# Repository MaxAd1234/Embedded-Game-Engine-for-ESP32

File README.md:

# Realization of an embedded game engine using real-time operating systems

This is a game engine for ESP32 boards demonstrating how real-time operating systems (RTOSs) and their concepts can be used for game development on microcontrollers. The game engine is part of my bachelor's thesis. It can be used as a base for developing games on microcontrollers like the ESP32.

## Demos

### Bird Game

### Pong clone

## Features
The game engine supports the following features:
- 2D-Tilemap-Rendering
- Four different input types (press, release, hold and hold for a specific time)
- Texture and audio storage
- 8-bit-style audio support for background music and sound effects
- Box and circle colliders
- Simple physics for gravity and forces
- Game programming interface
- Game objects as the base for game elements
- 2D Vectors
- Dynamic frame rate adaptation

## Tech Stack
- ESP-IDF
- C++
- FreeRTOS
- KiCad for the PCB

## Table of Contents

- [Demos](#demos)
- [Features](#features)
- [Getting Started](#getting-started)
  - [Hardware prerequisites](#hardware-prerequisites)
  - [Software prerequisites](#software-prerequisites)
  - [Example games](#example-games)
  - [How to set up](#how-to-set-up)
  - [Coordinate system](#coordinate-system)
- [How the Game Engine works](#how-the-game-engine-works)
  - [Architecture](#architecture)
  - [Input handling](#input-handling)
- [Components and features](#components-and-features)
  - [Input](#input)
  - [Graphics](#graphics)
  - [Audio](#audio)
  - [Collision](#collision)
  - [Physics](#physics)
  - [Level Design](#level-design)
  - [Game objects](#game-objects)
  - [Main Game Interface](#main-game-interface)
- [Further documentation and architecture](#further-documentation-and-architecture)
- [License](#license)

## Getting Started
### Hardware prerequisites
The game engine was built for a handheld using the following parts. Other parts could be used, but eventually the code needs to be adapted (e.g., the panels and the data bus configuration must be changed when using another display).

**Used parts**
- 6 push buttons
- DFRobot ESP32-P4
- 240x320 pixel, 2.8-inch display with 8-bit parallel interface and ILI9341 driver
- Active Piezo buzzer

You can connect the parts however you want. During prototyping I first used a breadboard. After this I designed a PCB and soldered the parts to it. You can find the Gerber files [here](hardware/pcb/) and the used wiring [here](hardware/wiring/wiring.pdf).

### Software prerequisites

- ESP-IDF v6.0
- FreeRTOS V10.5.1
- Display driver: [`espressif/esp_lcd_ili9341`](https://components.espressif.com/components/espressif/esp_lcd_ili9341). The dependency is declared in `main/idf_component.yml` so it should be automatically downloaded during the build. Otherwise you can install the driver like this:

```bash
idf.py add-dependency "espressif/esp_lcd_ili9341"
```

### Example games

Currently there are two example games included in this repository. Each game contains comments explaining its setup and how the game engine is used. The first game side-scrolling bird game called [Bird Game](games/bird_game/), inspired by a well-known mobile game. It demonstrates how to use the physics to imitate natural jumping and gravity. The second game is a [Pong](games/pong/)-style game demonstrating how to use several scenes in the game engine to create e.g., menu scenes or different game modes.

All graphics and sounds of the examples were created by me. This project is not affiliated with the original games.

### How to set up 

Replace the corresponding engine files with the files from the game folders. The files have the same names as the files in the game engine.

To flash the game onto the handheld, run:

```bash
idf.py -p PORT flash
```

### Coordinate system

> [!IMPORTANT]
>
>The origin of every game object, tile or texture matches the origin of the screen.
>
>Usually, the origin of a screen is its upper left corner. This means that the x-axis increases to the right and the y-axis increases downwards. But the screen used for building the handheld has its origin in the lower left corner, which is unusual. This has only a small effect on the game logic because only the y-axis changes in direction. But this has a bigger impact on the rendering. Usually textures are stored in top-down format that corresponds to the texture having its origin in the upper left corner. But because the screen's origin is in the lower left corner, textures stored in the top-down format are rendered upside down. That's because the screen always draws the texture with an origin at the lower left corner and if the texture is stored in top-down format, the origins are inverted.
>
>To solve this rendering issue, you currently have to store all textures in bottom-up format if you are using a screen with its origin in the lower left corner because I implemented the rendering primarily for screens with an origin at the upper left corner. In the future, textures will be always stored in top-down format and the rendering will be configurable to match the screen.
>
>Also when you are using screens with their origin in the lower left corner, you have to increase the y-coordinate of an object to move it up.
>If you want to use a screen with it's origin in the upper left corner you can store textures in top-down format, you have to increase the y-coordinate to lower objects and you have to change the position of the [upper and lower screen border objects](engine/components/World/World.cpp) for a working collision detection with the screenborders.

## How the Game Engine works

### Architecture

The engine's functions are divided among dedicated tasks. There are five tasks:

#### Init-Task

The Init-Task initializes the game state. It runs once after starting the handheld and is then deleted. To make sure it runs first, the Init-Task has a priority of 20 (highest in the engine).

#### Logic-Task

The Logic-Task is for updating and running the game, so it functions as the main loop. It processes input, updates the game for the elapsed time and generates a snapshot of the current game state to send it to the Rendering-Task for rendering. It is a periodic task running every 1/FPS seconds. Its priority is 4.

#### Rendering-Task

The Rendering-Task renders the newest game state if one is available. It is also a periodic task running every 1/FPS seconds. It has a priority of 3, so the Logic-Task runs first and a game state is always available for rendering.

#### Audio-Task 

The Audio-Task plays the game audio. It receives the audio to play from the Logic-Task as a pointer to the sound-data. It supports two audio channels for background music and "normal" sound effects. The background music only plays when no "normal" sound effect is set to play. When there is background music, but a sound effect is played, the background music keeps advancing. The Audio-Task is a periodic task with a period of 5 ms and a priority of 6, so the audio output can be quite smooth.

#### Statistics-Task 

The Statistics-Task is for adapting the frame rate of the game dynamically. For this, the Rendering-Task and Logic-Task measure their execution time, so the possible frame rate can be calculated by adding them. After calculating and adding some buffer time, the Statistics-Task checks whether there are deadline misses or transfer misses (a transfer miss means that the transfer of a frame did not end before the next rendering loop, which means that the frame rate is too fast and the video data output can't be supported by the hardware). If there are misses or the possible frame rate including the buffer is lower than the set frame rate, the frame rate will be reduced. When there are no misses and the possible frame rate is higher than the set frame rate, the frame rate will be increased. The dynamic adapting of the frame rate makes the gameplay smoother when the frame rate is set too high because it removes flickering through lowering the frame rate and it improves and makes the video smoother through increasing the frame rate as high as possible. It has a priority of 5 and runs periodically.

### Input handling

Input is provided by using interrupts. For each button, an interrupt is registered reacting to both falling and rising edges. The interrupt handler creates an input event when the interrupt is triggered. The event contains the input type (press or release), which button was responsible for the interrupt, and the event time. Queues are used for communication between the interrupt handlers and the tasks, and between the tasks.

### Components and features
The game engine contains different components that can be used for programming games. All components and functions that can be used for creating games are described here.

> [!NOTE]
> **Getters and setters:** Most members listed in the tables below have a getter and a setter. They are not listed in the tables. They are named `get` and `set` followed by the member's name with a capital first letter, e.g., `getMovingSpeed()` and `setMovingSpeed(int speed)` for `movingSpeed`. Some getters return a reference, so the member can be changed directly, e.g., `getDirection().setX(1.0f)`. The members of the `World` class are accessed with `getRegister()`, `getTileMap()`, `getInput()` and `getAudio()`. For more details, refer to the code.

#### Input

##### `BUTTON_TYPE` (enum)

Used for identifying the buttons in the interrupt handlers and for navigating in the `InputService`.

| Values |
|--------|
| `A_BUTTON` |
| `B_BUTTON` |
| `ARROW_UP_BUTTON` |
| `ARROW_DOWN_BUTTON` |
| `ARROW_RIGHT_BUTTON` |
| `ARROW_LEFT_BUTTON` |

##### `InputService` (class)

For processing the input events created by the interrupt handler and using the input for the game logic.

| Field | Description |
|-------|-------------|
| `Button buttons[6]` | Array containing objects of the `Button` class. This class is used for internal management of a button state. The array manages all inputs. A `BUTTON_TYPE` can be used to request the data of the corresponding button. |
| `size_t buttonCount` | Count of all buttons. Only for internal use. |

| Method | Parameters | Description |
|--------|------------|-------------|
| `void resetInputAfterFrame()` | None | Resets the button states after each frame. Through this function, e.g., a button press is only valid for one frame. For internal use only. |
| `void resetInput()` | None | Resets all button states to the initial button state. Can be used, for example, for a level change. |
| `bool wasButtonReleased()` | `BUTTON_TYPE button` | Returns true when a button was released. |
| `bool wasButtonPressed()` | `BUTTON_TYPE button` | Returns true when a button was pressed. |
| `bool isButtonHeld()` | `BUTTON_TYPE button` | Returns true when a button is held. |
| `bool wasButtonHeldFor()` | `BUTTON_TYPE button, uint64_t time` | Returns true when a button was held for X microseconds. If the button was held for the given time, the internal timestamps are consumed and further calls of the function will always return false. So always check for the longest time first. |

#### Graphics

##### `Texture` (class)

For pixel values, the RGB565 format is used. Every pixel is described by 16 bits.

| Field | Description |
|-------|-------------|
| `const uint16_t* sprite` | Pointer to the bitmap of the texture. When it has `nullptr` as value, it is an empty texture and will not be rendered. |
| `const uint16_t* bitMask` | Pointer to the bit mask of the texture. Every value in the bit mask defines if the pixel of the bitmap at the corresponding position will be rendered. The bit mask can be used to make textures have other shapes than only rectangles. When it has `nullptr` as value, every pixel of the bitmap is rendered. |
| `int heigth` | Height of the texture. When a wrong height is assigned to the texture, undefined behavior will occur. |
| `int width` | Width of the texture. When a wrong width is assigned to the texture, undefined behavior will occur. |

| Method | Parameters | Description |
|--------|------------|-------------|
| `Texture()` | None | Default constructor. Constructs an empty texture without bitmap, bit mask, width and height. |
| `Texture()` | `const uint16_t* sprite, const uint16_t* bitMask, int width, int heigth` | Constructor. Constructs a texture with the passed parameters. |
| `const uint16_t* getSprite()` | None | Returns the pointer to the bitmap of the texture. |
| `const uint16_t* getBitMask()` | None | Returns the pointer to the bit mask of the texture. |
| `uint16_t getPixel()` | `int row, int col` | Returns the pixel of the bitmap at the given position. The bitmap is a row-major array. |
| `int getWidth()` | None | Returns the width of the texture. |
| `int getHeigth()` | None | Returns the height of the texture. |

#### Audio

##### `Tone` (struct)

| Field | Description |
|-------|-------------|
| `unsigned int frequency` | Frequency of the tone. To use a tone as a pause, set the frequency to 0. |
| `uint64_t durationInMs` | Duration of the tone. |

##### `Sound` (class)

| Field | Description |
|-------|-------------|
| `Tone* sound` | Pointer to a tone array. The tone array is the definition of the sound. |
| `unsigned int toneCount` | Length of the tone array. |
| `bool isLooped` | True when the sound is a loop. |
| `unsigned int priority` | Priority of the sound. Can be used to define which sound will be played when several sounds are triggered to play in a frame. |
| `bool canBeOverridenBySamePrio` | True when the same priority can override a sound. |

| Method | Parameters | Description |
|--------|------------|-------------|
| `Sound()` | None | Default constructor. |
| `Sound()` | `Tone* _sound, unsigned int _toneCount, bool _isLooped, unsigned int priority, bool canBeOverridenBySamePrio` | Constructor. Creates a `Sound` object with the passed parameters. |

##### `AudioService` (class)

| Method | Parameters | Description |
|--------|------------|-------------|
| `AudioService()` | None | Default constructor. |
| `void setSoundeffect()` | `Sound* newEffect` | Sets the passed `Sound` as the next sound to be played if the passed pointer is not a `nullptr` and the priority of the sound is higher than the priority of the last set sound effect within the frame. Will replace the current playing sound. |
| `void setBackgroundMusic()` | `Sound* newBackgroundMusic` | Sets the passed `Sound` as the next background music to be played if the passed pointer is not a `nullptr` and the priority of the sound is higher than the priority of the last set background music within the frame. Will replace the current playing sound. |

#### Collision

##### `COLLISION_TYPE` (enum)

Used for movement with collision. Defines types which can stop a moving game object when it is colliding with an object of this type. Has 5 base types. To add your own types, just extend the [enum](engine/components/Colliders/includes/collisiontypes.hpp).

| Values |
|--------|
| `NONE` |
| `BLOCKED_BY_UPPER_DISPLAY_SIDE` |
| `BLOCKED_BY_LOWER_DISPLAY_SIDE` |
| `BLOCKED_BY_LEFT_DISPLAY_SIDE` |
| `BLOCKED_BY_RIGTH_DISPLAY_SIDE` |

##### `Collider` (class)

Abstract base class for colliders.

| Member | Description |
|--------|-------------|
| `int offsetX` | Offset in x-direction for the starting point of a collider. The usual start point of a collider is the origin of the `GameObject`. |
| `int offsetY` | Offset in y-direction for the starting point of a collider. The usual start point of a collider is the origin of the `GameObject`. |
| `bool isActive` | Determines if the collider is active. |
| `GameObject& owner` | Reference to the `GameObject` owning the `Collider`. Used for the position of the object to calculate collision. |
| `COLLISION_TYPE ownType` | `COLLISION_TYPE` of the collider. Is used for movement with collision. If another `GameObject`'s collider has this type in its `collidesWithTypes` list, it will stop moving when colliding with the `GameObject`. |
| `vector<COLLISION_TYPE> collidesWithTypes` | Stores the `COLLISION_TYPE`s the `owner` would collide with while moving. |

| Method | Parameters | Description |
|--------|------------|-------------|
| `bool isInVector()` | `COLLISION_TYPE type` | Returns true if `collidesWithTypes` contains `type`. |
| `Collider()` | `GameObject& _owner` | Constructs the collider with the passed `GameObject` as `owner`. |
| `Collider()` | `int _offsetX, int _offSetY, bool _isActive, GameObject& _owner, COLLISION_TYPE _ownType` | Constructs the collider with the passed parameters. |
| `void setOwnType()` | `COLLISION_TYPE typeToSet` | Sets `ownType` to `typeToSet`. |
| `COLLISION_TYPE getOwnType()` | None | Returns `ownType`. |
| `void addTypeToCollideWith()` | `COLLISION_TYPE typeToAdd` | Adds `typeToAdd` to `collidesWithTypes`. |
| `void deleteTypeToCollideWith()` | `COLLISION_TYPE typeToDelete` | Deletes `typeToDelete` from `collidesWithTypes`. |
| `virtual bool touchesAndOverlapsWith() = 0` | `Collider& otherCollider` | Returns true if the collider is touching or overlapping with `otherCollider`. |
| `virtual bool overlapsWith() = 0` | `Collider& otherCollider` | Returns true only if the collider is overlapping with `otherCollider`. |
| `void setActive()` | `bool active` | Sets `isActive` to the passed value. |
| `bool getIsActive()` | None | Returns `isActive`. |
| `vector<COLLISION_TYPE> getAllTypesThatObjectCollidesWith()` | None | Returns a copy of `collidesWithTypes`. |

##### `CircleCollider` (class)

Inherits from `Collider`.

| Member | Description |
|--------|-------------|
| `int radius` | Radius of the circle in pixels. |

**Hint:**
Collision detection uses the offsets as the center of the circle.

| Method | Parameters | Description |
|--------|------------|-------------|
| `CircleCollider()` | `GameObject& _owner` | Constructs a `CircleCollider` with the passed `GameObject` as `owner`. |
| `CircleCollider()` | `int _offsetX, int _offSetY, bool _isActive, GameObject& _owner, COLLISION_TYPE _ownType, int _radius` | Constructs a `CircleCollider` with the passed parameters. |

##### `BoxCollider` (class)

Inherits from `Collider`.

| Member | Description |
|--------|-------------|
| `int width` | Width of the box. |
| `int heigth` | Height of the box. |

| Method | Parameters | Description |
|--------|------------|-------------|
| `BoxCollider()` | `GameObject& _owner` | Constructs a `BoxCollider` with the passed `GameObject` as `owner`. |
| `BoxCollider()` | `int _offsetX, int _offSetY, bool _isActive, GameObject& _owner, COLLISION_TYPE _ownType, int width, int heigth` | Constructs a `BoxCollider` with the passed parameters. |

#### Physics

##### `Vector` (class)

Template class for 2D vectors.

| Member | Description |
|--------|-------------|
| `T x` | X component. |
| `T y` | Y component. |

| Method | Parameters | Description |
|--------|------------|-------------|
| `Vector()` | None | Constructs a vector with 0 as default values. |
| `Vector()` | `T xValue, T yValue` | Constructs a vector with the passed x and y values. |
| `float getLength()` | None | Returns the length of the vector. |
| `void normalize()` | None | Normalizes the vector only if the length is not zero. |

##### `Physics` (class)

| Member | Description |
|--------|-------------|
| `ActiveForce activeForces[MAX_ACTIVE_FORCES]` | Contains all forces affecting a `GameObject`. The size can be set by changing the definition of [`MAX_ACTIVE_FORCES`](engine/components/Physics/includes/Physics.hpp). |
| `int activeForceCount` | Count of forces affecting an object. |
| `float weight` | Weight of an object. Needed for calculating acceleration and movement created by the forces. Default value is 1. |
| `Vector<float> friction` | Friction in x and y direction. Is used to decrease the velocity created by forces. Works like a velocity against the velocity created by forces. Unit is pixel/s. |
| `float gravityForce` | Magnitude of the force affecting an object as gravity. Functions as the length of a vector. |
| `Vector<float> gravityDirection` | Contains only the set direction of the gravity. Is a normalized vector. |
| `bool _gravityEnabled` | Determines if gravity is enabled. |
| `bool _physicsEnabled` | Determines if forces are enabled. |

| Method | Parameters | Description |
|--------|------------|-------------|
| `Physics()` | None | Default constructor. |
| `Physics()` | `float _weight, float _gravityForce, Vector<float> _gravityDirection, Vector<float> _friction` | Constructs a `Physics` object with the passed parameters. Zero or negative values for the weight will be set to 1. |
| `void addForces()` | `Vector<float> direction, float force, float durationMs` | Adds a force that is active for `durationMs`. The `direction` will be normalized. The magnitude of the force functions as the length of the vector. |
| `void enableGravity()` | None | Enables gravity. |
| `void disableGravity()` | None | Disables gravity. |
| `void enablePhysics()` | None | Enables forces. |
| `void disablePhysics()` | None | Disables forces. |
| `void updatePhysics()` | `uint64_t deltaTime` | Updates all added forces for `deltaTime` milliseconds. For each force, it first calculates the acceleration. Then it adds the velocity created by multiplying the acceleration by `deltaTime` to the existing velocity of the object. |
| `void resetForceVelocity()` | None | Resets the velocity created by forces to 0. |
| `void resetGravity()` | None | Resets the velocity created by gravity to 0. |
| `void updateGravity()` | `uint64_t deltaTime` | Updates the velocity created by gravity for `deltaTime` milliseconds. |
| `void applyFriction()` | `uint64_t deltaTime` | Decreases the velocity created by the forces. |

#### Level Design

For designing the game scene, a tilemap is used. Because of the tilemap, textures can be reused, which saves flash memory. The tilemap is also used for efficient rendering because only tiles need to be rendered anew when, e.g., an object moves and the picture in a tile changes through the new position of the object.

##### `TileMap` (class)

| Member | Description |
|--------|-------------|
| `vector<Tile> tileMap` | Contains all tiles of the tilemap in row-major order. |
| `int rows` | Count of rows in the tilemap. |
| `int cols` | Count of columns in the tilemap. |
| `int tilesize` | Size of a tile side. Tiles are square. |

| Method | Parameters | Description |
|--------|------------|-------------|
| `TileMap()` | `int _rows, int _cols, int _tileSize` | Constructs a tilemap with the passed parameters. |
| `void setTileTexture()` | `Texture* _tex, int _row, int _col` | Sets the texture of a tile at the passed position in the tilemap. |
| `Tile getTile()` | `int _row, int _col` | Returns the tile at the passed position. |
| `Tile getTile()` | `int index` | Returns the tile at the passed index. |
| `bool checkIsInTile()` | `int _row, int _col, GameObject* object` | Returns true when the object is in the tile at the passed position. |
| `void tileNeedsRedraw()` | `int _row, int _col` | Marks the tile at the passed position as needing a redraw. |
| `void tileWasRedrawed()` | `int _row, int _col` | Marks the tile at the passed position as redrawn. |
| `void allTileNeedRedraw()` | None | Marks all tiles as needing a redraw. |

#### Game objects

Game objects are used as base game elements and as a basic internal interface for, e.g., rendering all game elements. Features and functions can be added through classes inheriting from `GameObject`.

##### `GameObject` (class)

| Member | Description |
|--------|-------------|
| `Vector<float> position` | Position of the object. |
| `Vector<float> movingDirection` | Direction of movement. |
| `int movingSpeed` | Speed of movement in pixel/s. |
| `bool isActive` | Specifies whether an object is active in the game. |
| `Physics physics` | Physics simulator of the object. |
| `Collider* collider` | Collider of the object. Can be a `BoxCollider` or `CircleCollider`. |
| `Texture texture` | Texture of the object. |

| Method | Parameters | Description |
|--------|------------|-------------|
| `GameObject()` | `Vector<float> _position` | Constructs an object at the passed position. |
| `GameObject()` | `Vector<float> _position, bool _isActive, int speed` | Constructs an object with the passed parameters. |
| `GameObject()` | `Vector<float> _position, Texture _texture` | Constructs an object with the passed parameters. |
| `GameObject()` | `Vector<float> _position, Texture _texture, bool _isActive` | Constructs an object with the passed parameters. |
| `GameObject()` | `Vector<float> _position, Texture _texture, bool _isActive, int speed` | Constructs an object with the passed parameters. |
| `void setBoxCollider()` | `int _width, int _heigth, int _offsetX, int _offsetY, bool _setActive, COLLISION_TYPE _ownType` | Adds a `BoxCollider` with the passed parameters to the game object. Any existing collider will be deleted. |
| `void setCircleCollider()` | `int _radius, int _offsetX, int _offsetY, bool _setActive, COLLISION_TYPE _ownType` | Adds a `CircleCollider` with the passed parameters to the game object. Any existing collider will be deleted. |
| `void deleteCollider()` | None | Deletes any existing collider. |
| `void resetDirection()` | None | Resets the direction to 0. |
| `bool touchesAndOverlapsWithOtherObject()` | `GameObject* other` | Returns true if the objects' colliders are touching or overlapping. Only returns true if both objects are active, both objects have colliders and both colliders are active. |
| `bool overlapsWithOtherObject()` | `GameObject* other` | Returns true only if the objects' colliders are overlapping. Only returns true if both objects are active, both objects have colliders and both colliders are active. |

#### Main Game Interface

##### `ObjectRegister` (class)

The object register is used for keeping track of all participating game objects. Only registered game objects will be considered, e.g., in rendering or movement with collision.

| Member | Description |
|--------|-------------|
| `vector<GameObject*> objectRegister` | List of all registered objects. |

| Method | Parameters | Description |
|--------|------------|-------------|
| `ObjectRegister()` | None | Default constructor. |
| `void insertIntoRegister()` | `GameObject* object` | Registers the passed object if it is not already in the register. |
| `void deleteFromRegister()` | `GameObject* object` | Deletes the object from the register if it is included. |
| `int getCountOfObjectsInRegister()` | None | Returns the count of objects in the register. |
| `GameObject* getObjectAt()` | `int index` | Returns the object at the passed index. |

##### `World` (class)

The `World` class is the main game class containing all game logic and behavior. Nearly all programming happens here.

| Member | Description |
|--------|-------------|
| `ObjectRegister objectRegister` | Register of the game. |
| `TileMap tileMap` | The game's tilemap. |
| `InputService& input` | The game's input service. |
| `AudioService& audio` | The game's audio service. |
| `int screenWidth, screenHeigth, tileSize` | Screen and tile dimensions. |
| `GameObject rightScreenBorder, leftScreenBorder, upperScreenBorder, lowerScreenBorder` | These objects' only purpose is collision with the screen borders. If a game object adds one of the screen borders to its `collidesWithTypes` list and movement with collision is used on this game object, it won't move when colliding with these objects. Because of this objects, there are always at least 4 objects registered in the `ObjectRegister`. |

**Note on the movement functions**

One main reason why a frame has to be rendered anew is that game objects change their positions and a new image is created through the new positions. Because the engine is using tile-based rendering, each tile has to be marked as needing a redraw when the part of the frame contained in the tile changes. Because of this, and because the `World` class owns the tilemap, different movement types for game objects are provided through this class.

| Method | Parameters | Description |
|--------|------------|-------------|
| `void init()` | None | Is used for initializing the game and all its game objects and other properties and states. Will only be called once upon starting the game engine when powering up the handheld. |
| `void update()` | `uint64_t deltaTime` | The game's update function. Will be called once every frame and updates the game for the time passed since the last update. The game logic and behavior have to be implemented in this function. |
| `void moveObjectTo()` | `GameObject* object, Vector<float> newPos` | Moves the object to the new position only if it is active. Triggers all tiles at the old and new position to redraw, like every movement function. |
| `void moveObjectWithoutCollision()` | `GameObject* object, uint64_t deltaTime` | Moves the object in the object's movement direction with its speed without considering collision, only if the object is active. |
| `void moveObjectWithCollision()` | `GameObject* object, uint64_t deltaTime` | Moves the object in the object's movement direction with its speed, considering all `COLLISION_TYPE`s added to the object's collider's `collidesWithTypes`, only if the object is active. When the object is colliding with another object whose collision type is in `collidesWithTypes`, the movement stops. |
| `void triggerTileMapToCheckRedraw()` | `GameObject* o` | All tiles that contain the object's texture are marked as needing a redraw. Can be used for own use cases and game functions where the screen has to be rendered new afterwards. |
| `void moveWithPhysicsWithoutCollision()` | `GameObject* object, uint64_t deltaTime, bool gravityOrForce` | Moves the object through the velocities created by physics, only if it's active and physics are enabled. When `gravityOrForce` is true, the velocity created by forces is used, otherwise the velocity created by gravity. |
| `void moveWithPhysicsWithCollision()` | `GameObject* object, uint64_t deltaTime` | Moves the object through the velocities created by physics, only if it's active and physics are enabled. Considers collision. When `gravityOrForce` is true, the velocity created by forces is used, otherwise the velocity created by gravity. |
| `void moveBy()` | `GameObject* object, Vector<float> movedBy` | Moves the object by the passed vector. |
| `void moveByWithCollision()` | `GameObject* object, Vector<float> movedBy, int steps` | Moves the object by the passed vector. Considers collision. |
| `void changeTexture()` | `GameObject* object, Texture tex` | Changes the texture of the game object and triggers the tiles containing the object to redraw. |
| `bool collidesWithType()` | `GameObject* object, COLLISION_TYPE type` | Returns true if the object is colliding with another object of the collision type. |
| `void onFirstCollisionWithType()` | `GameObject* object, COLLISION_TYPE type, void (*func)(void*), void* args` | Calls the passed function once when colliding with another object of the passed collision type. The call is triggered by the first found object that is colliding with the passed object and has the passed collision type. |
| `void onAllCollisionWithType()` | `GameObject* object, COLLISION_TYPE type, void (*func)(void*), void* args` | Checks collision with every other active object in the game. When there is a collision and the other object has the passed collision type, the passed function gets called. |
| `void setActivateOfGameObject()` | `GameObject* object, bool val` | Sets the value of the active state of the passed object and triggers all tiles containing the object to redraw. |

#### Engine configuration

To change pins or settings for the frame rate adaptation, change the definitions in the [engine config file](engine/main/EngineConfig.h)

### Further documentation and architecture

For further insights, refer to the source code. For further documentation of the internal functions of the engine, the design, the architecture and the evaluation, refer to my bachelor's thesis:

- [German version (original)](docs/thesis_german.pdf)
- [English version (machine-translated)](docs/thesis_english.pdf)

## License

This project is licensed under the MIT License. See the [LICENSE](LICENSE) file for details.

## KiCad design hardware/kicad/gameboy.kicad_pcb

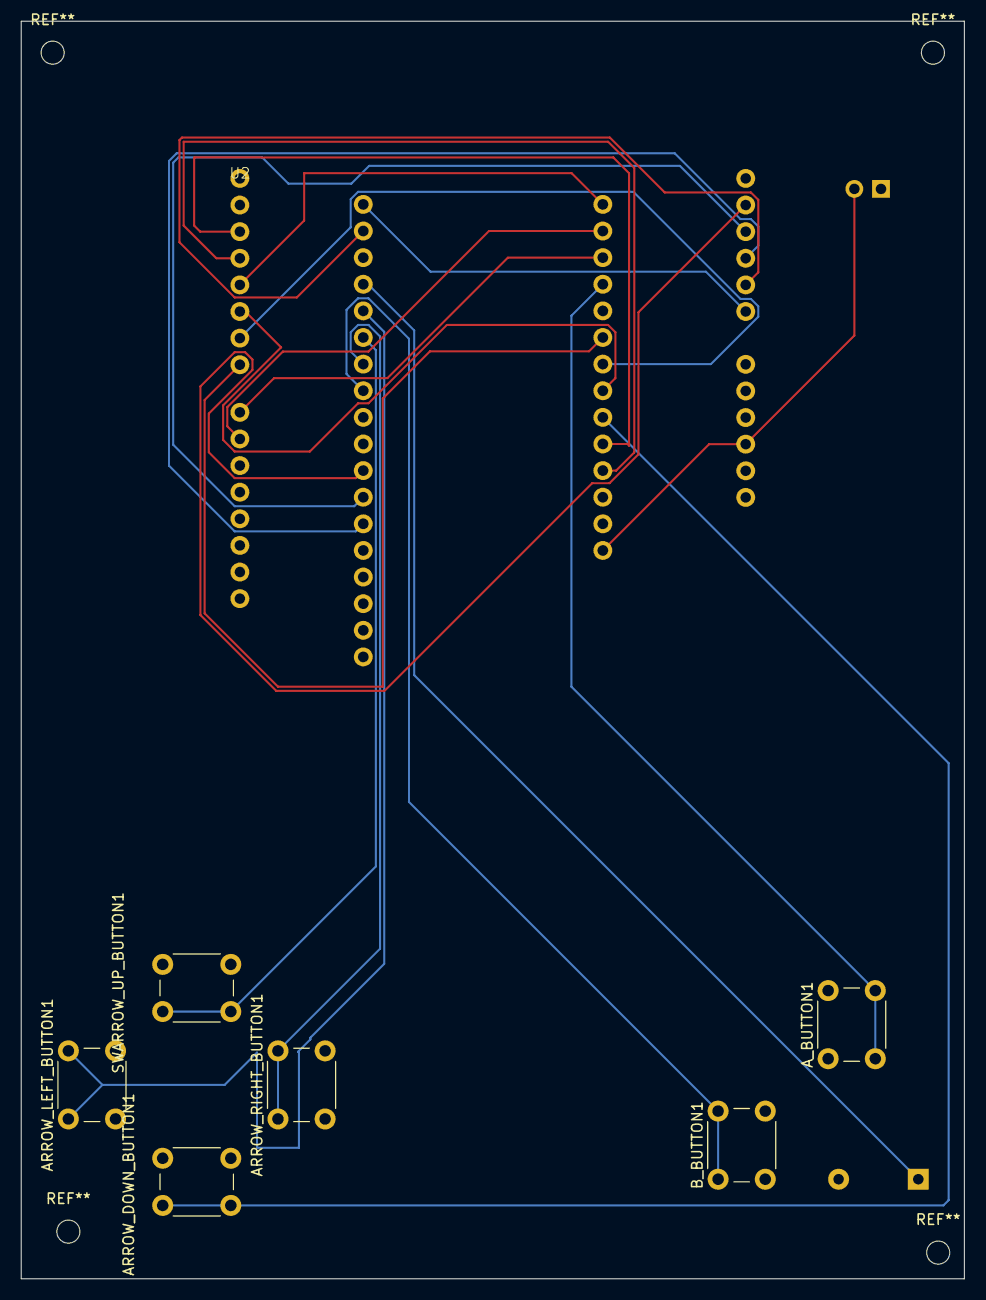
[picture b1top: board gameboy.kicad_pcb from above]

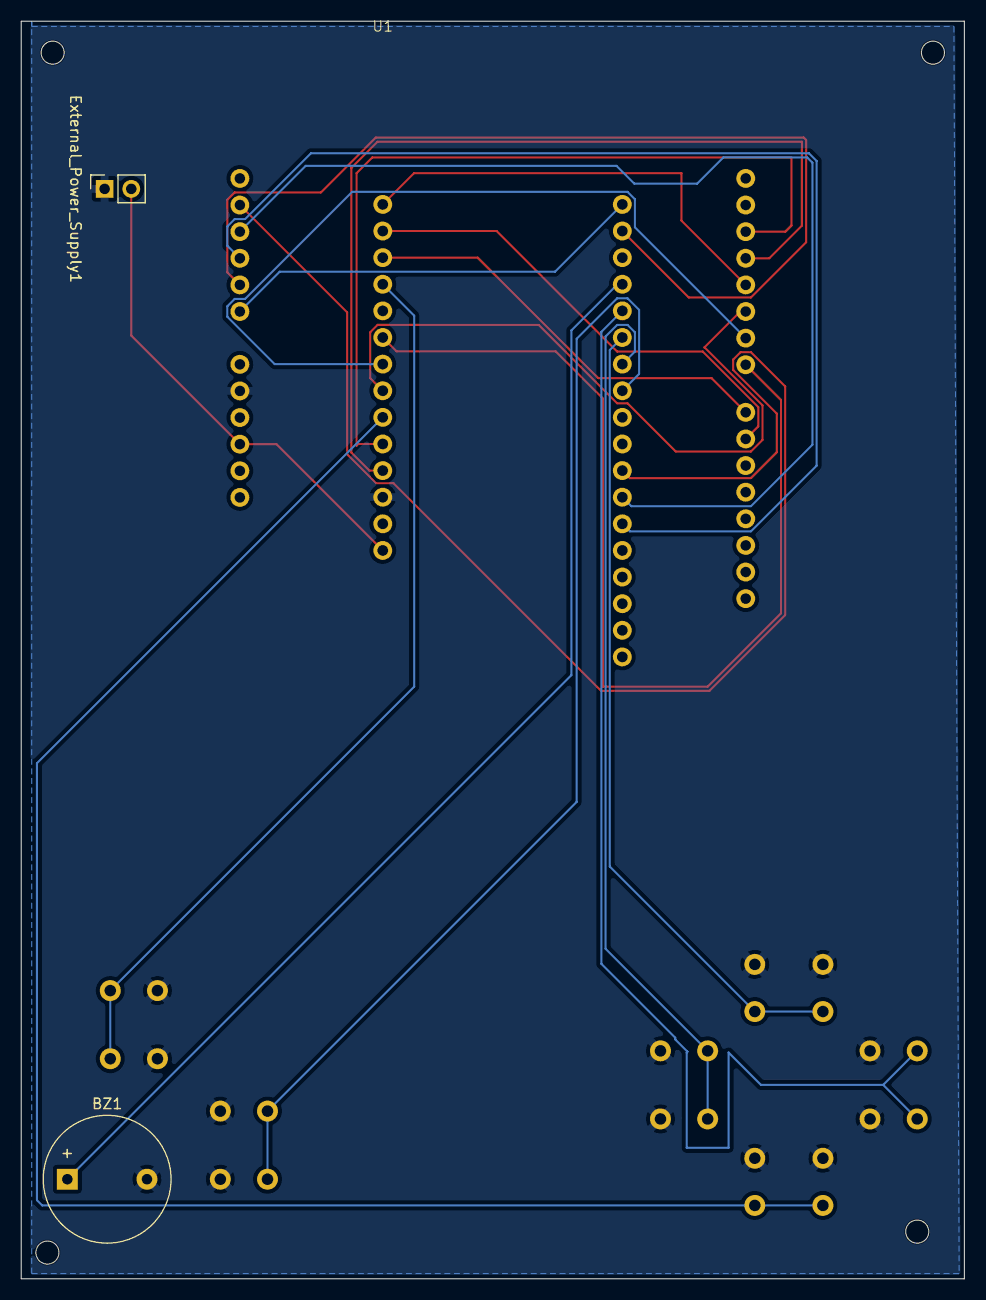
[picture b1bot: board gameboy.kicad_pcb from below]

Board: 2 copper layers, 90.0 x 120.0 mm, 10 parts (3 on the bottom side), 22 nets.

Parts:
ARROW_DOWN_BUTTON1: SW_Push; SW_PUSH_6mm_H5mm
ARROW_LEFT_BUTTON1: SW_PUSH_6mm_H5mm
ARROW_RIGHT_BUTTON1: SW_PUSH_6mm_H5mm
A_BUTTON1: SW_Push; SW_PUSH_6mm_H5mm
BZ1: Buzzer; Buzzer_12x9.5RM7.6
B_BUTTON1: SW_PUSH_6mm_H5mm
External_Power_Supply1: Conn_01x02; PinSocket_1x02_P2.54mm_Vertical
SWARROW_UP_BUTTON1: SW_PUSH_6mm_H5mm
U1: Untitled
U2: Untitled_1

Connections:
/A: A_BUTTON1.2, U1.4 (GPIO_36)
/B: B_BUTTON1.1, U1.22 (GPIO_48)
/BUZZ: BZ1.1 (+), U1.18 (GPIO_4)
/CS: U1.26 (GPIO_29), U2.19 (LCD_CS)
/D0: U1.3 (GPIO_35), U2.9 (LCD_D0)
/D1: U1.2 (GPIO_34), U2.10 (LCD_D1)
/D2: U1.10 (GPIO_33), U2.3 (LCD_D2)
/D3: U1.11 (GPIO_32), U2.4 (LCD_D3)
/D4: U1.1 (GPIO_31), U2.5 (LCD_D4)
/D5: U1.8 (GPIO_23), U2.6 (LCD_D5)
/D6: U1.7 (GPIO_22), U2.7 (LCD_D6)
/D7: U1.6 (GPIO_21), U2.8 (LCD_D7)
/DOWN: ARROW_DOWN_BUTTON1.2, U1.9 (GPIO_51)
/LEFT: ARROW_LEFT_BUTTON1.1, U1.19 (GPIO_52)
/RD: U1.15 (GPIO_38/R), U2.22 (LCD_RD)
/RIGHT: ARROW_RIGHT_BUTTON1.1, U1.21 (GPIO_49)
/RS: U1.27 (GPIO_28), U2.20 (LCD_RS)
/RST: U1.25 (GPIO_30), U2.18 (LCD_RST)
/UP: SWARROW_UP_BUTTON1.1, U1.20 (GPIO_50)
/VIN: External_Power_Supply1.2, U1.14 (VCC), U2.27 (5V)
/WR: U1.16 (GPIO_37/T), U2.21 (LCD_WR)
GND: ARROW_DOWN_BUTTON1.1, ARROW_LEFT_BUTTON1.2, ARROW_RIGHT_BUTTON1.2, A_BUTTON1.1, BZ1.2 (-), B_BUTTON1.2, External_Power_Supply1.1, SWARROW_UP_BUTTON1.2, U1.12 (GND), U2.25 (GND)
